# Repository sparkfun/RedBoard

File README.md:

SparkFun RedBoard Qwiic
============================

[  
*SparkFun RedBoard Qwiic (DEV-15123)*](https://www.sparkfun.com/products/15123)

At SparkFun we continually like to inovate, update, and improve even when it comes to our very own development boards. We have multiple versions of the SparkFun RedBoard in our catalog but none of them in an R3 form factor with a Qwiic connector on it to make I2C easy… until now! The SparkFun RedBoard Qwiic is an Arduino-compatible development board that uses a few of the features that we have loved about Arduinos of the past while also incorporating a few key improvements over the original RedBoard. The best part about the RedBoard Qwiic is that (as the name implies) it utilizes our handy Qwiic Connect System which means no soldering or shields are required to connect it to the rest of your system!

The RedBoard can be programmed over a USB Mini-B cable using the Arduino IDE: Just plug in the board, select "Arduino UNO" from the board menu and you're ready to upload code.

Repository Contents
-------------------
* **/Documentation** - Data sheets, additional product information
* **/Hardware** - Eagle design files (.brd, .sch)
* **/Production** - Production panel files (.brd)

Documentation
--------------
* **[Hookup Guide](https://learn.sparkfun.com/tutorials/redboard-qwiic-hookup-guide)** - Basic hookup guide for the Redboard.
* **[SparkFun Fritzing repo](https://github.com/sparkfun/Fritzing_Parts)** - Fritzing diagrams for SparkFun products.
* **[SparkFun 3D Model repo](https://github.com/sparkfun/3D_Models)** - 3D models of SparkFun products. 

License Information
-------------------

This product is _**open source**_! 

Please review the LICENSE.md file for license information. 

If you have any questions or concerns on licensing, please contact techsupport@sparkfun.com.

Distributed as-is; no warranty is given.

- Your friends at SparkFun.

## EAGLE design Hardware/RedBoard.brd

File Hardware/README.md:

SparkFun Redboard Design Files
=====================================

The .sch and .brd files hare are Eagle CAD schematic and PCB design files from SparkFun Electronics.
A freeware version of Eagle can be found [here](http://www.cadsoftusa.com/download-eagle/freeware/).

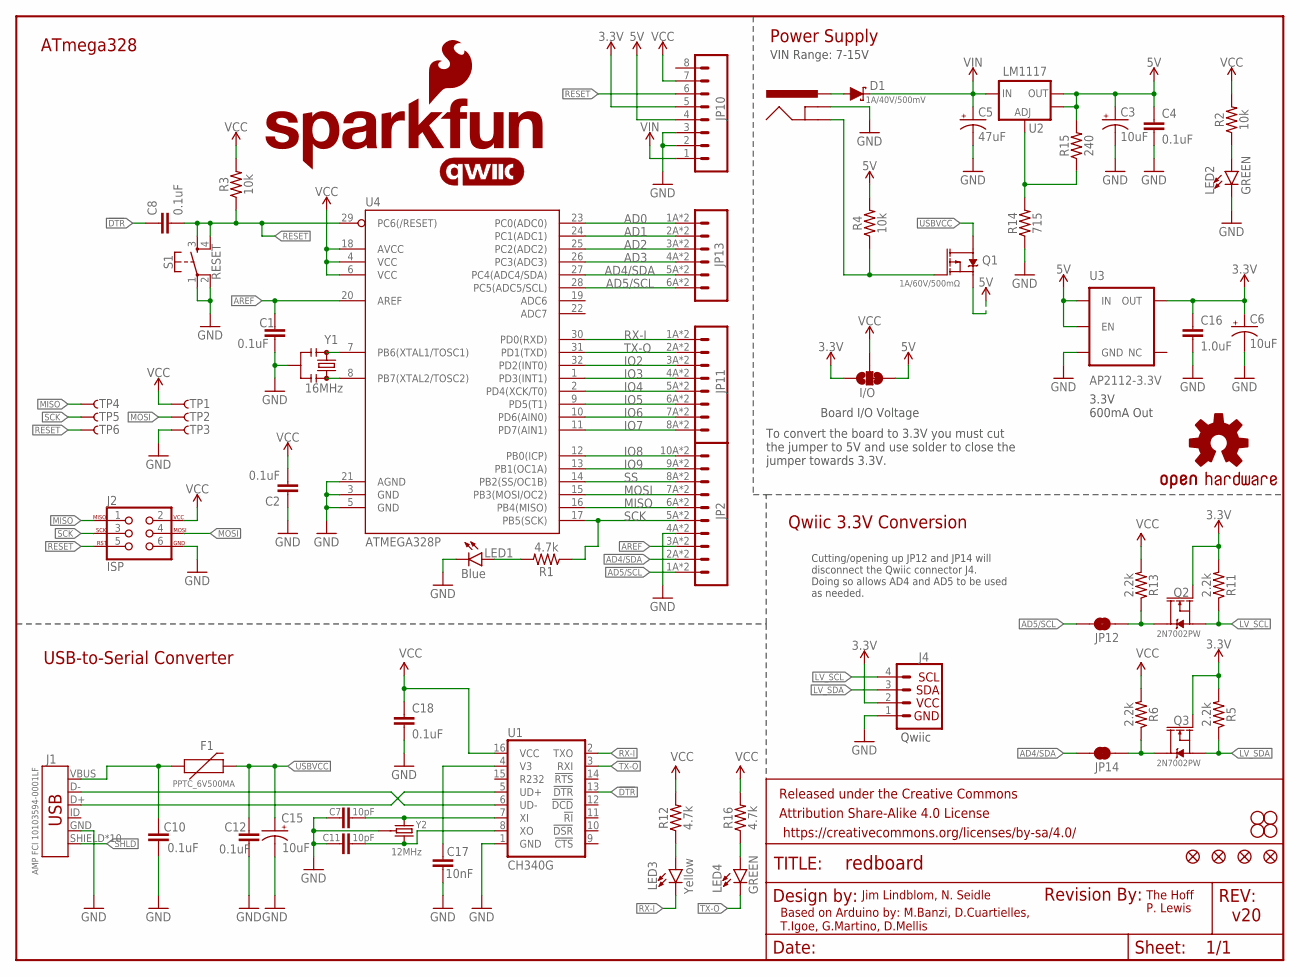
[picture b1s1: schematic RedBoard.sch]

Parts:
C1, C2, C4, C8, C10, C12, C18: 0.1uF; 0603
C3, C6, C15: 10uF; EIA3216
C5: 47uF; PANASONIC_D
C7, C11: 10pF; 0603
C16: 1.0uF; 0603-CAP
C17: 10nF; 0603-CAP
D1: 1A/40V/500mV; SMA-DIODE
F1: PPTC_6V500MA; 0805
FRAME2: FRAME-LETTER; CREATIVE_COMMONS
I/O: JUMPER-SMT_3_1-NC_TRACE_SILK; SMT-JUMPER_3_1-NC_TRACE_SILK
J1: AMP FCI 10103594-0001LF; USB-MICROB-PTH-MILL
J2: ISP; 2X3_SMT_POSTS
J3: POWER_JACKSUPER_BOMB_DIGITY; POWER_JACK_SMD_OVERPASTE_SUPER_BOMB_DIGITY
J4: QWIIC_CONNECTORJS-1MM; 1X04_1MM_RA
JP2: M10SMD_COMBO; 1X10_SMD_COMBINED
JP3, JP4, JP5, JP6: STAND-OFF
JP8, JP9, JP15, JP16: FIDUCIAL1X2; FIDUCIAL-1X2
JP10: CONN_08SMD-COMBO-FEMALE; 1X08_SMD_COMBINED
JP11: JP11; 1X08_SMD_COMBINED@1
JP12, JP14: JUMPER-SMT_2_NC_TRACE_SILK; SMT-JUMPER_2_NC_TRACE_SILK
JP13: M06SMD-STRAIGHT-COMBO; 1X06_SMD_STRAIGHT_COMBO
LED1: Blue; LED-1206-HIDDENSILK
LED2: GREEN; LED-1206-HIDDENSILK
LED3: Yellow; LED-1206-HIDDENSILK
LED4: GREEN; LED-1206
LOGO1: REVISION
LOGO2: SFE_LOGO_NAME_FLAME.1_INCH; SFE_LOGO_NAME_FLAME_.1
LOGO3: QWIIC_LOGO_5MM; QWIIC_5MM
Q1: 1A/60V/500mΩ; SOT23-3
Q2, Q3: 2N7002PW; SOT323
R1, R12, R16: 4.7k; 0603
R2, R3, R4: 10k; 0603
R5, R6, R11, R13: 2.2k; 0603
R14: 715; 0603
R15: 240; 0603
S1: RESET; TACTILE_SWITCH_SMD_5.2MM
TP1, TP2, TP3, TP4, TP5, TP6: TP-3x5; PAD.03X.05
U1: CH340G; SO016
U2: LM1117; SOT223-ALT1
U3: AP2112-3.3V; SOT23-5
U4: ATMEGA328P; TQFP32-08
U$16: OSHW-LOGOS; OSHW-LOGO-S
Y1: 16MHz; RESONATOR-SMD-3.2X1.3
Y2: 12MHz; CRYSTAL-SMD-3.2X2.5

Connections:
3.3V: C6.+, C16.1, I/O.1, J4.2, JP10.5, Q2.1 (G), Q3.1 (G), R5.2, R11.2, U3.5 (OUT)
5V: C3.+, C4.1, I/O.3, JP10.4, Q1.2 (S), R4.2, R15.2, U2.2 (OUT), U2.4 (OUT), U3.1 (IN), U3.3 (EN)
!DTR: C8.1, U1.13 (!DTR)
AD0: JP13.1A (1), JP13.1B (1), U4.23 (PC0(ADC0))
AD1: JP13.2A (2), JP13.2B (2), U4.24 (PC1(ADC1))
AD2: JP13.3A (3), JP13.3B (3), U4.25 (PC2(ADC2))
AD3: JP13.4A (4), JP13.4B (4), U4.26 (PC3(ADC3))
AD4/SDA: JP2.2A (2), JP2.2B (2), JP13.5A (5), JP13.5B (5), JP14.2, U4.27 (PC4(ADC4/SDA))
AD5/SCL: JP2.1A (1), JP2.1B (1), JP12.2, JP13.6A (6), JP13.6B (6), U4.28 (PC5(ADC5/SCL))
AREF: C1.1, JP2.3A (3), JP2.3B (3), U4.20 (AREF)
GND: C1.2, C2.1, C3.-, C4.2, C5.-, C6.-, C7.1, C10.2, C11.1, C12.2, C15.-, C16.2, C17.2, C18.2, J1.GND, J2.6, J3.GND (GNDBREAK), J4.1, JP2.4A (4), JP2.4B (4), JP10.2, JP10.3, LED1.C, LED2.C, R14.1, S1.1, S1.2, TP3.P$1, U1.1 (GND), U3.2 (GND), U4.3 (GND), U4.5 (GND), U4.21 (AGND), Y1.2, Y2.2 (GND), Y2.4 (GND)
INSERT: J3.P$4 (GND), Q1.1 (G), R4.1
IO2: JP11.3A (3), JP11.3B (3), U4.32 (PD2(INT0))
IO3: JP11.4A (4), JP11.4B (4), U4.1 (PD3(INT1))
IO4: JP11.5A (5), JP11.5B (5), U4.2 (PD4(XCK/T0))
IO5: JP11.6A (6), JP11.6B (6), U4.9 (PD5(T1))
IO6: JP11.7A (7), JP11.7B (7), U4.10 (PD6(AIN0))
IO7: JP11.8A (8), JP11.8B (8), U4.11 (PD7(AIN1))
IO8: JP2.10A (10), JP2.10B (10), U4.12 (PB0(ICP))
IO9: JP2.9A (9), JP2.9B (9), U4.13 (PB1(OC1A))
LV_SCL: J4.4, Q2.2 (S), R11.1
LV_SDA: J4.3, Q3.2 (S), R5.1
MISO: J2.1, JP2.6A (6), JP2.6B (6), TP4.P$1, U4.16 (PB4(MISO))
MOSI: J2.4, JP2.7A (7), JP2.7B (7), TP2.P$1, U4.15 (PB3(MOSI/OC2))
unnamed: LED1.A, R1.2
unnamed: LED2.A, R2.1
unnamed: U4.7 (PB6(XTAL1/TOSC1)), Y1.1
unnamed: U4.8 (PB7(XTAL2/TOSC2)), Y1.3
unnamed: LED4.A, R16.1
unnamed: C17.1, U1.4 (V3)
unnamed: JP12.1, Q2.3 (D), R13.1
unnamed: JP14.1, Q3.3 (D), R6.1
unnamed: LED3.A, R12.1
unnamed: C11.2, U1.8 (XO), Y2.3 (2)
unnamed: C7.2, U1.7 (XI), Y2.1
unnamed: J1.D-, U1.6 (UD-)
unnamed: J1.D+, U1.5 (UD+)
unnamed: R14.2, R15.1, U2.1 (ADJ)
PWRIN: D1.A, J3.VIN0 (PWR)
RESET: C8.2, J2.5, JP10.6, R3.1, S1.3, S1.4, TP6.P$1, U4.29 (PC6(/RESET))
RX-I: JP11.1A (1), JP11.1B (1), LED3.C, U1.2 (TXO), U4.30 (PD0(RXD))
SCK: J2.3, JP2.5A (5), JP2.5B (5), R1.1, TP5.P$1, U4.17 (PB5(SCK))
SHLD: J1.SHIELD, J1.SHIELD2 (SHIELD), J1.SHIELD3 (SHIELD), J1.SHIELD4 (SHIELD), J1.SHIELD5 (SHIELD), J1.SHIELD6 (SHIELD), J1.SHIELD7 (SHIELD), J1.SHIELD8 (SHIELD), J1.SHIELD9 (SHIELD), J1.SHIELD10 (SHIELD)
SS: JP2.8A (8), JP2.8B (8), U4.14 (PB2(SS/OC1B))
TX-O: JP11.2A (2), JP11.2B (2), LED4.C, U1.3 (RXI), U4.31 (PD1(TXD))
USBVCC: C12.1, C15.+, F1.2, Q1.3 (D)
VCC: C2.2, C18.1, I/O.2, J2.2, JP10.7, R2.2, R3.2, R6.2, R12.2, R13.2, R16.2, TP1.P$1, U1.16 (VCC), U4.4 (VCC), U4.6 (VCC), U4.18 (AVCC)
VIN: C5.+, D1.C, JP10.1, U2.3 (IN)
VUSB: C10.1, F1.1, J1.VBUS

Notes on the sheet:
Power Supply
ATmega328
USB-to-Serial Converter
Based on Arduino by: M.Banzi, D.Cuartielles, T.Igoe, G.Martino, D.Mellis
Jim Lindblom, N. Seidle
v20
VIN Range: 7-15V
3.3V 600mA Out
Board I/O Voltage
To convert the board to 3.3V you must cut the jumper to 5V and use solder to close the jumper towards 3.3V.
Qwiic
Qwiic 3.3V Conversion
Cutting/opening up JP12 and JP14 will disconnect the Qwiic connector J4. Doing so allows AD4 and AD5 to be used as needed.
The Hoff
P. Lewis

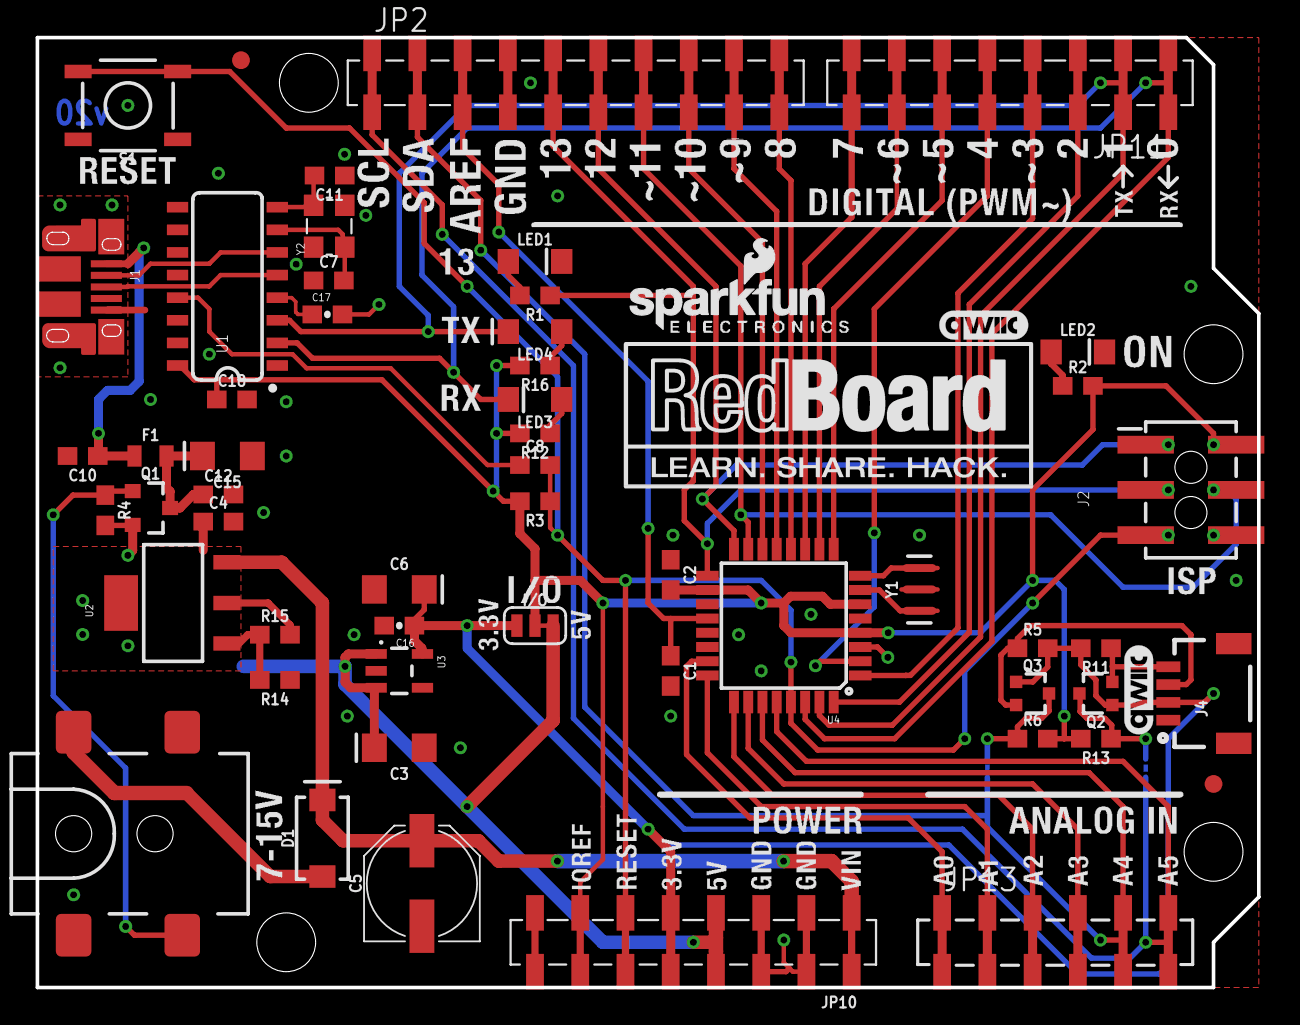
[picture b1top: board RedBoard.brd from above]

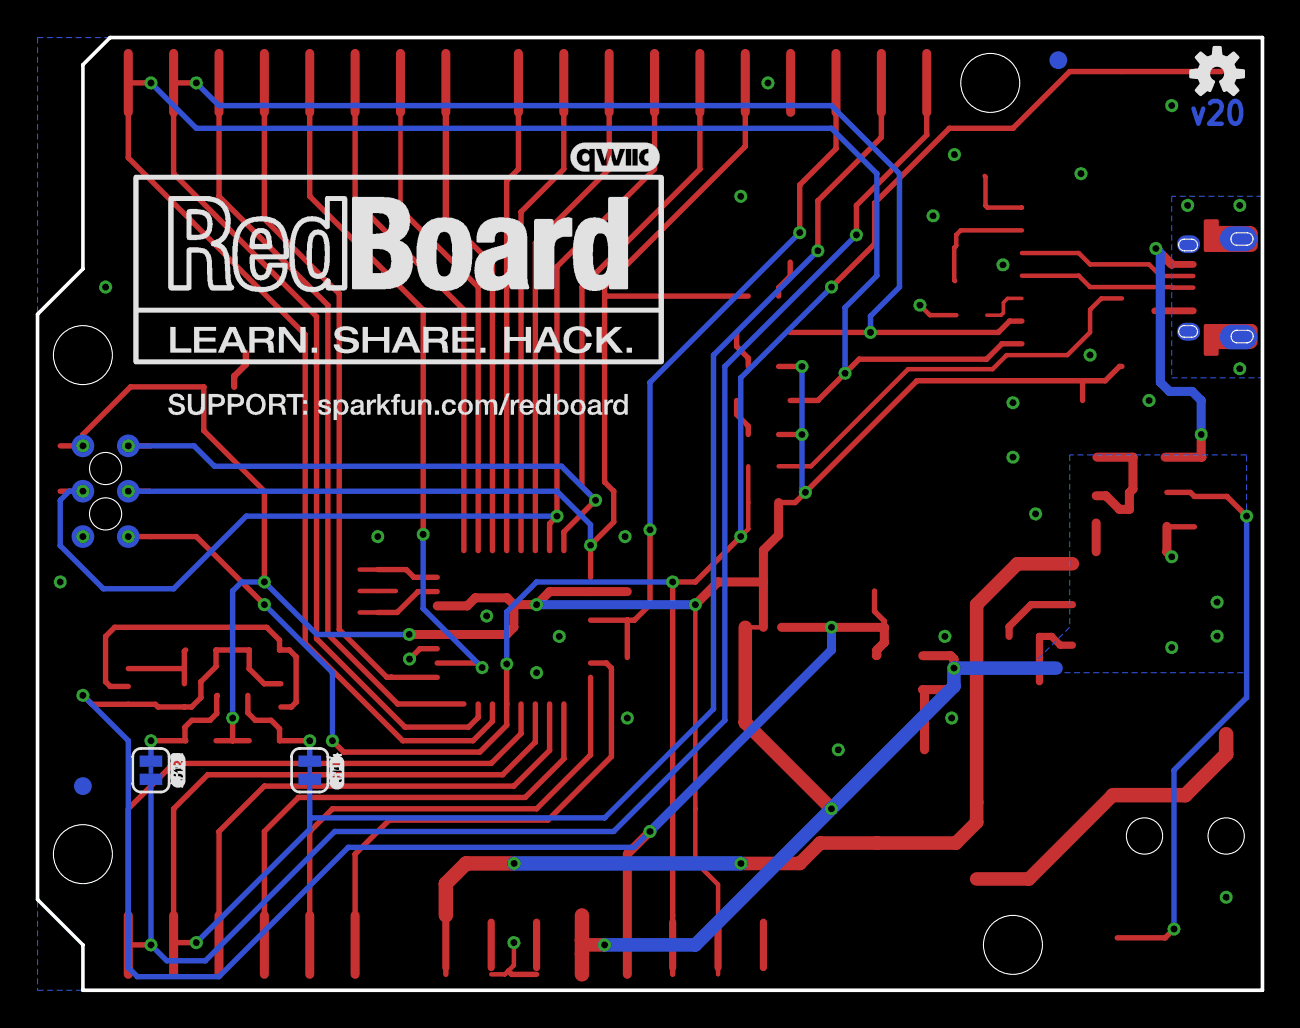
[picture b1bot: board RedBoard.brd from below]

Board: 2 copper layers, 68.6 x 53.3 mm, 77 parts (14 on the bottom side), 49 nets.

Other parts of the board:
LOGO4, LOGO5: QWIIC_LOGO_5MM; QWIIC_5MM
U$4: J120
U$9: J140

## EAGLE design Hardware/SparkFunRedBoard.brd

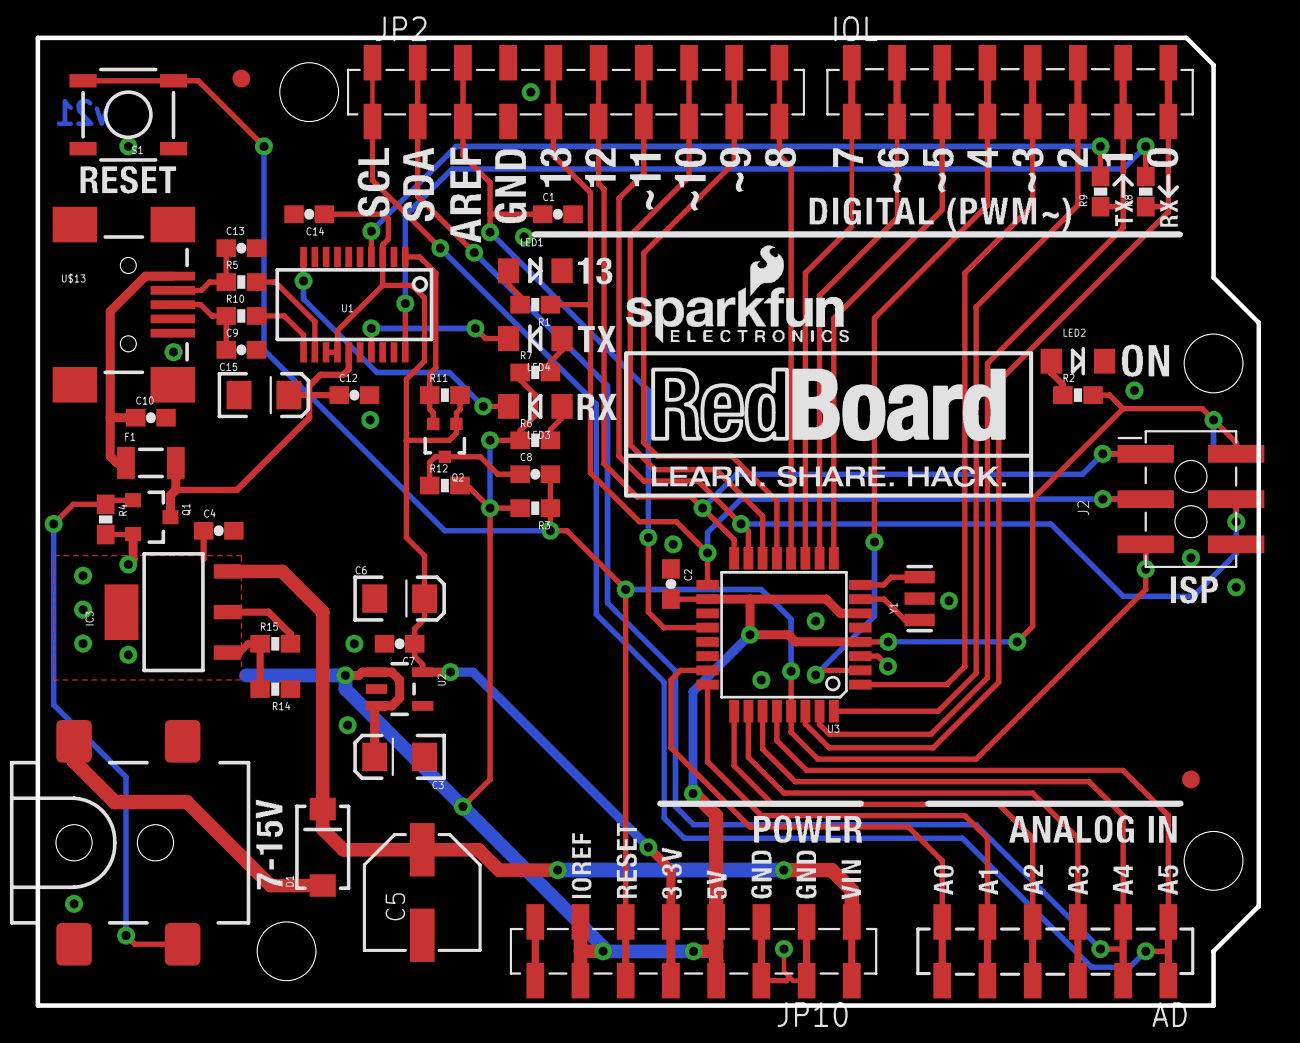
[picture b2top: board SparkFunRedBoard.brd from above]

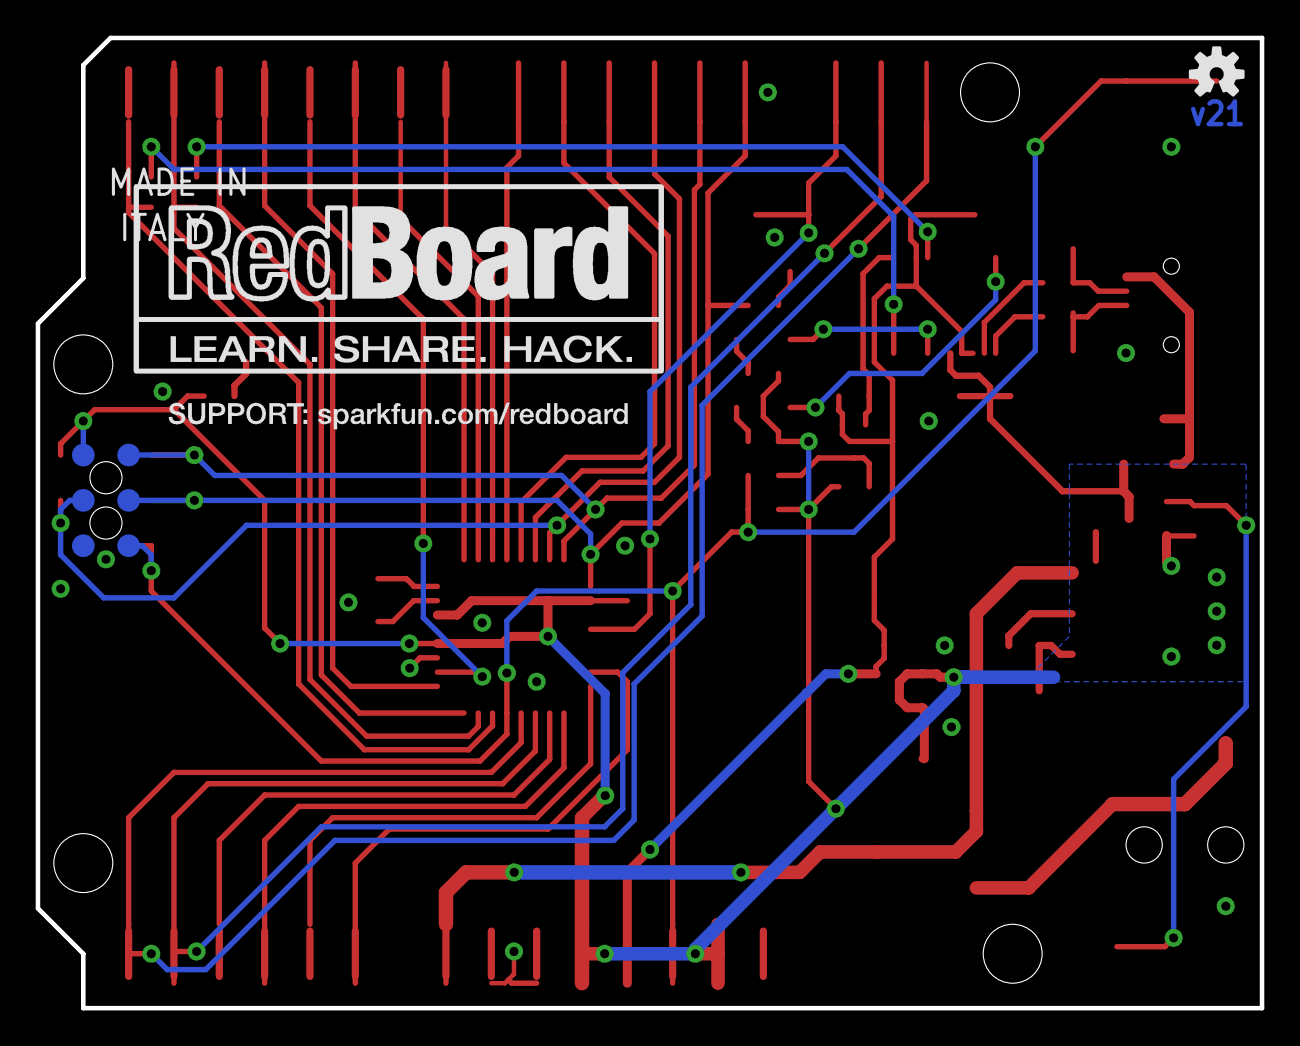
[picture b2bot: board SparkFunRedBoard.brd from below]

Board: 2 copper layers, 68.6 x 54.4 mm, 65 parts (7 on the bottom side), 47 nets.

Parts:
AD: 1X06_SMD_STRAIGHT_COMBO
C1, C2, C4, C8, C10, C12, C14: 0.1uF; 0603-CAP
C3, C6, C15: 10uF; EIA3216
C5: 47uF; PANASONIC_D
C7: 1uF; 0603-CAP
C9, C13: 47pF; 0603-CAP
D1: MBRA140; SMA-DIODE
F1: 500mA; PTC-1206
FRAME2: FRAME-LETTER; CREATIVE_COMMONS
IC3: LM1117; SOT223-ALT1
IOL: 1X08_SMD_COMBINED
J1: POWER_JACKOVERPASTE_REDBOARD_0603; POWER_JACK_SMD_OVERPASTE_REDBOARD_0603
J2: ICSP; 2X3_SMT_POSTS
JP1: LOGO-SFENW2; SFE-NEW-WEB
JP2: M10SMD_COMBO; 1X10_SMD_COMBINED
JP3, JP4, JP5, JP6: STAND-OFF
JP7: LOGO-SFESK; SFE-LOGO-FLAME
JP8, JP9: FIDUCIAL1X2; FIDUCIAL-1X2
JP10: 1X08_SMD_COMBINED
LED1: Blue; LED-1206-NO_SILK
LED2: Green; LED-1206-NO_SILK
LED3: Red; LED-1206-NO_SILK
LED4: Yellow; LED-1206-NO_SILK
Q1: ZXMP6A13FTA; SOT23-3
Q2: 2N7002PW; SOT323
R1, R2, R6, R7, R8, R9: 1k; 0603-RES
R3, R4, R11, R12: 10k; 0603-RES
R5, R10: 27; 0603-RES
R14: 715; 0603-RES
R15: 240; 0603-RES
S1: RESET; TACTILE_SWITCH_SMD
TP1, TP2, TP3, TP4, TP5, TP6: TP-3x5; PAD.03X.05
U1: FT231XS; SSOP20_L
U2: MIC5205; SOT23-5
U3: ATMEGA328; TQFP32-08
U$13: USB-MINIB-5PIN; USB-MINIB
U$16: OSHW-LOGOS; OSHW-LOGO-S
Y1: 16MHz; RESONATOR-SMD

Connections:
3.3V: C6.A, C7.1, C14.1, JP10.5, Q2.1, R11.2, U1.3, U1.13, U1.14, U2.5
5V: C2.2, C3.A, C4.1, IC3.2, IC3.4, J2.2, JP10.4, JP10.7, Q1.2, R2.2, R3.2, R4.2, R6.1, R7.1, R12.2, R15.2, TP1.P$1, U2.1, U2.3, U3.4, U3.6, U3.18
AD0: AD.1, U3.23
AD1: AD.2, U3.24
AD2: AD.3, U3.25
AD3: AD.4, U3.26
AD4/SDA: AD.5, JP2.2A, JP2.2B, U3.27
AD5/SCL: AD.6, JP2.1A, JP2.1B, U3.28
AREF: C1.1, JP2.3A, JP2.3B, U3.20
D+: C9.1, R10.1, U$13.D+
D-: C13.1, R5.1, U$13.D-
DTR: C8.1, Q2.3, R12.1
GND: C1.2, C2.1, C3.C, C4.2, C5.-, C6.C, C7.2, C9.2, C10.2, C12.2, C13.2, C14.2, C15.C, J1.GND, J2.6, JP2.4A, JP2.4B, JP10.2, JP10.3, LED1.C, LED2.C, R14.1, S1.1, S1.2, TP3.P$1, U1.6, U1.16, U2.2, U3.3, U3.5, U3.21, U$13.GND, U$13.MTN1, U$13.MTN2, U$13.MTN3, U$13.MTN4, Y1.2
INSERT: J1.P$4, Q1.1, R4.1
IO2: IOL.3, U3.32
IO3: IOL.4, U3.1
IO4: IOL.5, U3.2
IO5: IOL.6, U3.9
IO6: IOL.7, U3.10
IO7: IOL.8, U3.11
IO8: JP2.10A, JP2.10B, U3.12
IO9: JP2.9A, JP2.9B, U3.13
MISO: J2.1, JP2.6A, JP2.6B, TP4.P$1, U3.16
MOSI: J2.4, JP2.7A, JP2.7B, TP2.P$1, U3.15
unnamed: LED1.A, R1.2
unnamed: LED2.A, R2.1
unnamed: U3.7, Y1.1
unnamed: U3.8, Y1.3
unnamed: R5.2, U1.12
unnamed: R10.2, U1.11
unnamed: LED3.A, R6.2
unnamed: LED4.A, R7.2
unnamed: Q2.2, R11.1, U1.1
unnamed: IC3.1, R14.2, R15.1
PWRIN: D1.A, J1.VIN0
RESET: C8.2, J2.5, JP10.6, R3.1, S1.3, S1.4, TP6.P$1, U3.29
RX-I: IOL.1, R8.1, U3.30
RXD: R9.2, U1.4
RXLED: LED4.C, U1.17
SCK: J2.3, JP2.5A, JP2.5B, R1.1, TP5.P$1, U3.17
SS: JP2.8A, JP2.8B, U3.14
TX-O: IOL.2, R9.1, U3.31
TXD: R8.2, U1.20
TXLED: LED3.C, U1.10
USBVCC: C12.1, C15.A, F1.2, Q1.3, U1.15
VIN: C5.+, D1.C, IC3.3, JP10.1
VUSB: C10.1, F1.1, U$13.VBUS

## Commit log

2014-01-27 v06 Hardware - Currently live files
2014-01-27 updating readme
2014-02-03 New SMD ICSP header, logo, FT231X, power select
2014-02-05 Switch RX/TX labels, updating back logo
2014-02-05 LEDs to 1206; new barrel jack fp; moved 5V vreg
2014-02-05 Spacing out caps and resistors
2014-03-03 Moved C1 cap around silk. Moved some top silk.
2014-03-03 Moving vias off programming test points
2014-03-04 Tailing in ISP header pins
2014-03-04 Back to old ISP. Tucked in the paste on edge pins
2014-03-05 Created v21 panel
    Giant!
2014-08-07 Adjustments to FT231X circuit. Package updates.
    - Disconnecting FTDI 3.3V (VCCIO) from ATmega328's 3.3V bus
    - Getting rid of MOSFET on DTR line. 5V, 10k pull-up does the job just
    fine.
    - Adding vias to ISP test points.
    - Tailing the dimensions of the board in a bit. Board is now
    Arduino-standard 2.1" tall (was 2.14")
2014-08-11 upping version number to v22`
2014-08-13 reverting back to old DTR circuit
2015-03-20 corrected folder name
2015-06-22 Adding svg/pdf of Redboard, adding license and .git files, updating readme
2015-12-09 moved panel fiducials. board unchanged
2016-06-27 Schematic cleanup and minor updates post-checklist.
2016-06-27 Updating libraries where they don't affect copper.
2016-06-27 Updating 2x3 connector to show pin position.
2016-07-06 Fixing LED silk, changing power LED resistor.
2016-07-19 Fixing PROD_ID on J2 and C10.
2016-08-23 Panel created
    Panel was created and pushed to git hub so Jim can look at it more
    thoroughly.
2017-02-20 Update README.md
    Fixing product links
2017-02-21 Component Values Updated for 3D Model
2018-11-09 Starting from BlackBoard x02
    Starting from BlackBoard x02
2018-11-21 Silk Changes and USB changes
2018-11-27 Design Review fixes to silk and componenet placement
    Design Review fixes to silk and componenet placement
2018-12-03 Post Checklist changes
    Addressed polarity opin markings, documentation items like revised by.
2018-12-04 Redboard Qwiic Bom/Package Update
    Several outdated packages were present in design. Packages updated and bom updated.
2018-12-07 panel
2019-01-07 Updated Prod ID of Green LED
    Updated Prod ID of Green LED - Was Green/Yellow, is now green.
2019-01-07 Revert "Updated Prod ID of Green LED"
    This reverts commit 7f3e58299cb6063360d5b40b06a29a7e7771cac4.
2019-01-07 Updated Green TX LED Prod ID
    Updated LED5 to Green TX LED Prod ID.
2019-04-01 Update Graphical Datasheet
    -Correct Port Name on Pin 10
    -update image
    -update SKU
    -Rename files based on the correction from Graphical Datasheet Repo
2020-08-21 Ch340G with external Oscilator and caps
    -Swapped out CH340C for the CH340G
    -Added external 12MHz Crystal and caps
    -bumped version to v20 in sch and brd
    -cleaned up schematic overlap/spacing
    -Aprooved DRC errors (wire stubs, dimension and some jumper trace overlaps)
2020-08-21 Corrected IOREF Arduino header pin
    -This header pin previously was routed to 5V (incorrect), but now it is correctly connected to VCC (aka the logic level of the microcontroller, as selected by "I/O" 3-way jumper).
2020-08-21 switched load capacitors to 10pF
2020-08-21 removed 4-way junction on RESET net
2020-08-22 Updated SFE and QWIIC logos to vector to help with cam job times
2020-08-28 tvalues cleanup for assembly sheet
2020-09-04 Production panel v20

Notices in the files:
parts and their libraries:
SparkFun-Aesthetics: Licensing: CC v3.0 Share-Alike You are welcome to use this library for commercial purposes.
SparkFun-Aesthetics: Released under the Creative Commons Attribution Share-Alike 4.0 License
SparkFun-Aesthetics: https://creativecommons.org/licenses/by-sa/4.0
